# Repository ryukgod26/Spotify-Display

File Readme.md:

# Spotify Display
This is a Spotify Display Project with which you can control your spotify. You can Play/Pause, forward and Backward the songs. I will add more features in future like managing playlists and shuffling playlists.

## Why
I created this Project to control my Songs playing on Spotify without touching my Phone. This Become easier and feels better to control Songs with a separate display with Physical Buttons. This Project helped me learn how to use Spotify API.

## Zine

## BOM(Bill Of Materials)
|Name| Quantity| Total Cost (USD) | Link | Distributor|
|----|---------|------------------|------|------------|
| Esp32 C3 Mini | 1 | $2.5 | [Link](https://robu.in/product/esp32-c3-development-board-with-soldering/?gad_source=1&gad_campaignid=21296336107&gclid=CjwKCAjw3ejRBhAdEiwADkqPny-qgi54L9slNDuyxyBi9_V4dJO201Za-CnGg5tMcDLZ9UxwxrNwXBoC-5kQAvD_BwE) | Robu |
| TFT Display | 1 | $6.7 | [Link](https://robu.in/product/2-4-inch-spi-interface-240x320-touch-screen-tft-display-module/) | Robu |
| Push Buttons | 10 | $0.15 | [Link](https://robu.in/product/6x6x5-tactile-push-button-switch/) | Robu |
| Rotatry Encoder | 1 | $0.6 | [Link](https://robu.in/product/green-rotary-encoder-module-for-arduino-without-demo-code/) | Robu |

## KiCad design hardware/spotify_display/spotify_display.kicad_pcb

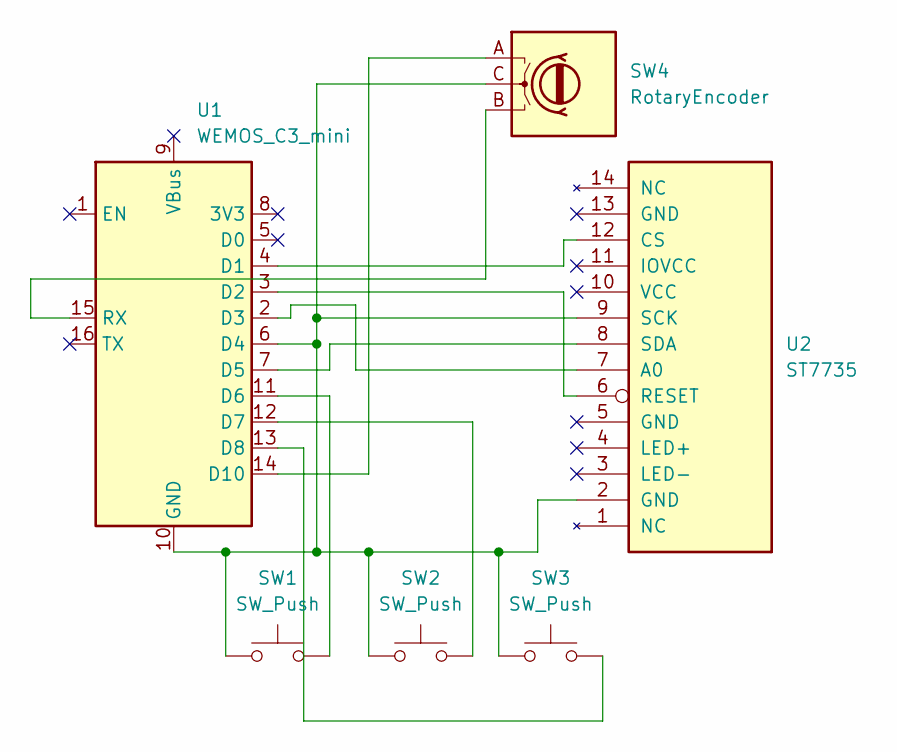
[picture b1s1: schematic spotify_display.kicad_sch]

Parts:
SW1, SW2, SW3: SW_Push; SW_Cherry_MX_1.00u_PCB
SW4: RotaryEncoder; RotaryEncoder_Alps_EC11E_Vertical_H20mm
U1: WEMOS_C3_mini
U2: ST7735; Display_ST7735

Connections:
unnamed: U1.4 (D1), U2.12 (CS)
unnamed: U1.3 (D2), U2.6 (RESET)
unnamed: U1.2 (D3), U2.7 (A0)
unnamed: SW1.1, SW2.1, SW3.1, SW4.C, U1.6 (D4), U1.10 (GND), U2.2 (GND), U2.9 (SCK)
unnamed: U1.7 (D5), U2.8 (SDA)
unnamed: SW1.2, U1.11 (D6)
unnamed: SW2.2, U1.12 (D7)
unnamed: SW3.2, U1.13 (D8)
unnamed: SW4.A, U1.14 (D10)
unnamed: SW4.B, U1.15 (RX)

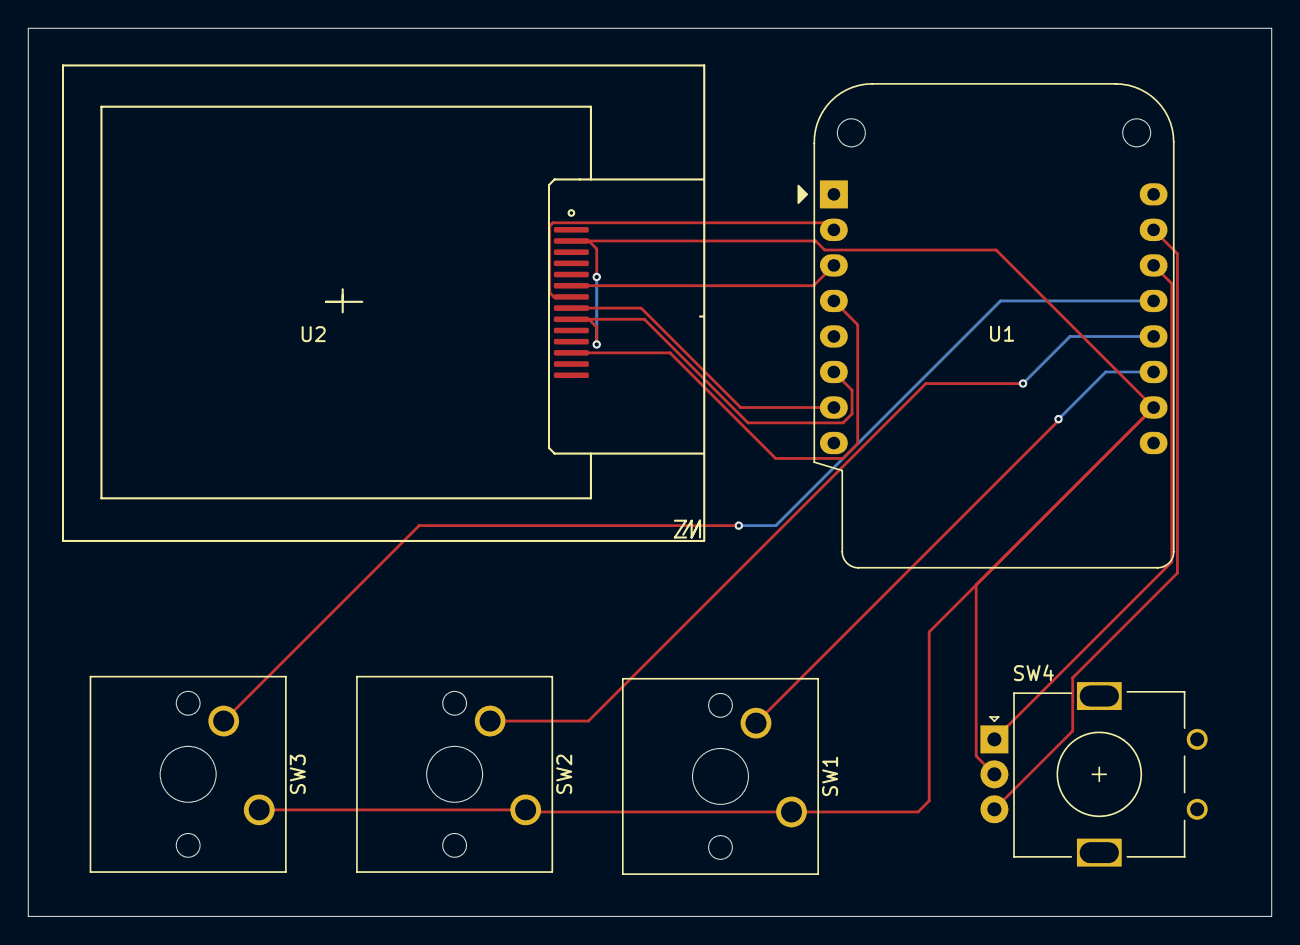
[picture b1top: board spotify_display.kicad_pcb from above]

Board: 2 copper layers, 88.9 x 63.5 mm, 6 parts (0 on the bottom side), 10 nets.

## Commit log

2026-03-18 Add new 3D model files for Spotify display
2026-05-14 Added Display and added a back panel
2026-05-14 Added Another wall in the case and joined the closer and also coded and understood the basic api code
2026-06-05 Maded new changes to the 3D Model and completed the 3D model
2026-06-06 Added Switches in the 3D Model
2026-06-06 Added hardware files like schematics and pcb
2026-06-22 Add Rotary Encoder component and update project files
    - Added a new Rotary Encoder symbol to the schematic with properties including reference, value, footprint, and description.
    - Updated the KiCad project configuration to specify the plot output directory.
    - Adjusted column widths in the project settings for better layout.
2026-06-22 Add zine image file to the repository
2026-06-23 Add BOM file and update README with Bill of Materials
